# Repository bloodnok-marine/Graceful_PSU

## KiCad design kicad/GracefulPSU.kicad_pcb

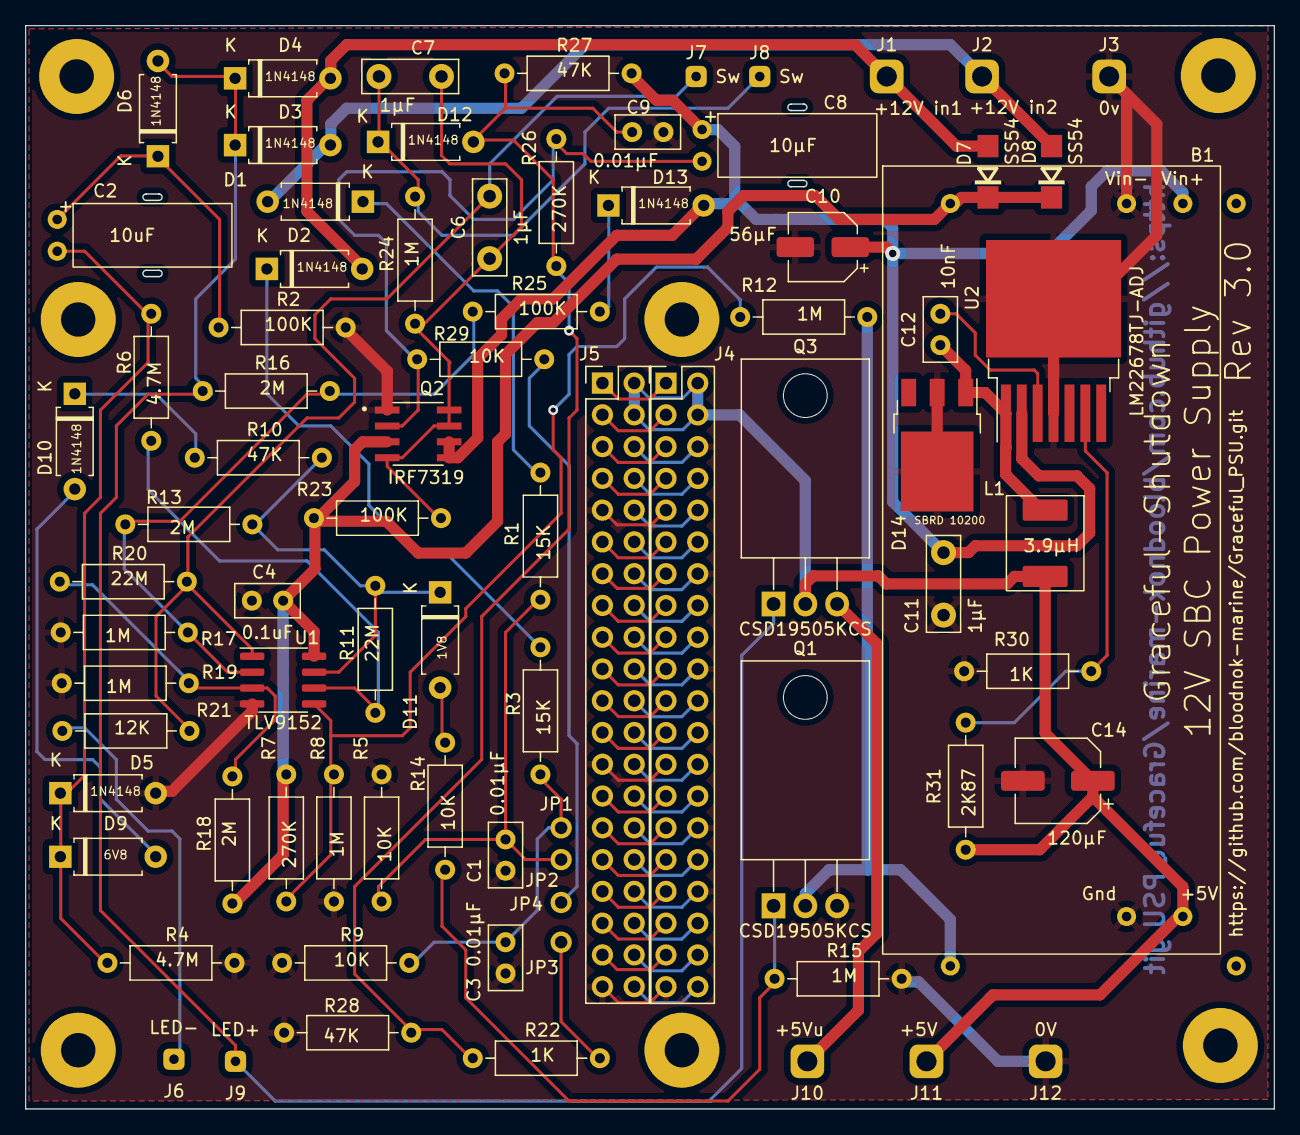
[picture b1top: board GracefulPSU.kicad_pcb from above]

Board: 2 copper layers, 99.8 x 86.6 mm, 88 parts (1 on the bottom side), 66 nets.

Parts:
B1: PSU_Board; Buck Power Supply Board
C1, C3, C9: 0.01μF; C_Disc_D5.0mm_W2.5mm_P2.50mm
C2: 10uF; Capacitor_THT_HorizRadial_D5_P2_H12
C4: 0.1uF; C_Disc_D5.0mm_W2.5mm_P2.50mm
C5: 1.6F; SuperCapacitor Module
C6, C7, C11: 1μF; C_Disc_D7.5mm_W2.5mm_P5.00mm
C8: 10μF; Capacitor_THT_HorizRadial_D5_P2_H12
C10: 56μF; CP_Elec_5x5.3
C12: 10nF; C_Disc_D5.0mm_W2.5mm_P2.50mm
C14: 120μF; CP_Elec_6.3x5.9
D1, D2, D3, D4, D5, D6, D10, D12, D13: 1N4148; my_diode_7.62_h
D7, D8: SS54; DO-214AC
D9: 6V8; my_diode_7.62_h
D11: 1V8; my_diode_7.62_h
D14: SBRD 10200; TO-252-3_TabPin2
H1, H2, H8: (no value)
H3, H4, H5, H6: pihole
J1: +12V in1; SolderConnector - HighCurrent
J2: +12V in2; SolderConnector - HighCurrent
J3: 0v; SolderConnector - HighCurrent
J4, J5: Conn_02x20; PinHeader_2x20_P2.54mm_Vertical
J6: LED-; SolderConnector
J7, J8: Sw; SolderConnector
J9: LED+; SolderConnector
J10: +5Vu; SolderConnector - HighCurrent
J11: +5V; SolderConnector - HighCurrent
J12: 0V; SolderConnector - HighCurrent
JP1, JP2, JP3, JP4: Jumper; Half-Jumper
L1: 3.9μH; Shenzhen MWSA0604S
Q1, Q3: CSD19505KCS; TO-220-3_Horizontal_TabDown
Q2: IRF7319; SOIC127P600X175-8N
R1, R3: 15K; my_resistor_6.3_2.5_10.16
R2, R23, R25: 100K; my_resistor_6.3_2.5_10.16
R4, R6: 4.7M; my_resistor_6.3_2.5_10.16
R5, R9, R14, R29: 10K; my_resistor_6.3_2.5_10.16
R7, R26: 270K; my_resistor_6.3_2.5_10.16
R8, R12, R15, R17, R19, R24: 1M; my_resistor_6.3_2.5_10.16
R10, R27, R28: 47K; my_resistor_6.3_2.5_10.16
R11, R20: 22M; my_resistor_6.3_2.5_10.16
R13, R16, R18: 2M; my_resistor_6.3_2.5_10.16
R21: 12K; my_resistor_6.3_2.5_10.16
R22, R30: 1K; my_resistor_6.3_2.5_10.16
R31: 2K87; my_resistor_6.3_2.5_10.16
U1: TLV9152; SOIC-8_3.9x4.9mm_P1.27mm
U2: LM22678TJ-ADJ; TO-263-7_TabPin8

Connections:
+5V: B1.1 (+5V), C14.1, J4.2, J4.4, J5.2, J5.4, J11.1, L1.2, Q3.2 (D), R31.2
GND: B1.2 (Gnd), B1.4 (Vin-), C1.1, C3.2, C4.2, C9.2, C10.2, C11.2, C14.2, D5.2 (A), D14.2 (A), J3.1, J4.6, J4.9, J4.14, J4.20, J4.25, J4.30, J4.34, J4.39, J5.6, J5.9, J5.14, J5.20, J5.25, J5.30, J5.34, J5.39, J12.1, Q1.3 (S), Q2.1 (S1), R2.2, R4.2, R5.1, R8.2, R9.1, R15.2, R17.2, R19.2, R28.2, R30.2, U1.4 (V-), U2.4 (GND), U2.8 (GND)
unnamed: B1.3 (Vin+), C8.1, C10.1, C11.1, D13.2 (A), Q2.5 (D2), Q2.6 (D2), R27.2, U2.2 (VIN)
unnamed: C1.2, JP2.1 (A), R1.2, R5.2
unnamed: C2.1, D6.1 (K), R2.1
unnamed: C2.2, D5.1 (K), D9.1 (K), R4.1, R6.1
unnamed: C3.1, JP1.1 (A), R3.2, R9.2
unnamed: C4.1, C5.1, D7.1 (K), D8.1 (K), Q2.3 (S2), R7.1, R18.1, R23.1, U1.8 (V+)
unnamed: C5.2, Q1.2 (D), R12.2
unnamed: C6.1, C7.1, Q2.4 (G2), Q2.7 (D1), Q2.8 (D1), R23.2, R24.1
unnamed: C6.2, J7.1, R20.2, R21.2, U1.1
unnamed: C7.2, D12.1 (K), J8.1, R24.2
unnamed: C8.2, Q2.2 (G1), R26.1, R29.1
unnamed: C9.1, D12.2 (A), R22.1, R26.2, R27.1, R28.1
unnamed: C12.1, U2.3 (BOOT)
unnamed: C12.2, D14.1 (K), L1.1, U2.1 (SW)
unnamed: D1.1 (K), R1.1
unnamed: D1.2 (A), D3.2 (A), D8.2 (A), J2.1
unnamed: D2.1 (K), R3.1
unnamed: D2.2 (A), D4.2 (A), D7.2 (A), J1.1
unnamed: D3.1 (K), D4.1 (K), D6.2 (A), J9.1, Q3.1 (G), R16.1
unnamed: D10.1 (K), R10.1
unnamed: D9.2 (A), D10.2 (A)
unnamed: D11.1 (K), R10.2, R11.2, R13.1, U1.7
unnamed: D11.2 (A), R14.1
unnamed: D13.1 (K), R25.2
unnamed: J4.1, J5.1
unnamed: J4.3, J5.3
unnamed: J4.5, J5.5
unnamed: J4.7, J5.7
unnamed: J4.8, J5.8
unnamed: J4.10, J5.10
unnamed: J4.11, J5.11
unnamed: J4.12, J5.12
unnamed: J4.13, J5.13
unnamed: J4.15, J5.15
unnamed: J4.16, J5.16
unnamed: J4.17, J5.17
unnamed: J4.18, J5.18
unnamed: J4.19, J5.19
unnamed: J4.21, J5.21
unnamed: J4.22, J5.22
unnamed: J4.23, J5.23
unnamed: J4.24, J5.24
unnamed: J4.26, J5.26
unnamed: J4.27, J5.27
unnamed: J4.28, J5.28
unnamed: J4.29, J5.29
unnamed: J4.31, J5.31
unnamed: J4.32, J5.32
unnamed: J4.33, J5.33
unnamed: J4.35, J5.35
unnamed: J4.36, J5.36
unnamed: J4.37, J5.37
unnamed: J4.38, J5.38
unnamed: J4.40, J5.40
unnamed: J6.1, R21.1
unnamed: J10.1, Q3.3 (S)
unnamed: JP3.1 (A), R22.2
unnamed: JP4.1 (A), R29.2
unnamed: Q1.1 (G), R14.2, R15.1
unnamed: R6.2, R11.1, U1.6 (-)
unnamed: R7.2, R8.1, R12.1, U1.5 (+)
unnamed: R13.2, R16.2, R17.1, R25.1, U1.2 (-)
unnamed: R18.2, R19.1, R20.1, U1.3 (+)
unnamed: R30.1, R31.1, U2.6 (FB)

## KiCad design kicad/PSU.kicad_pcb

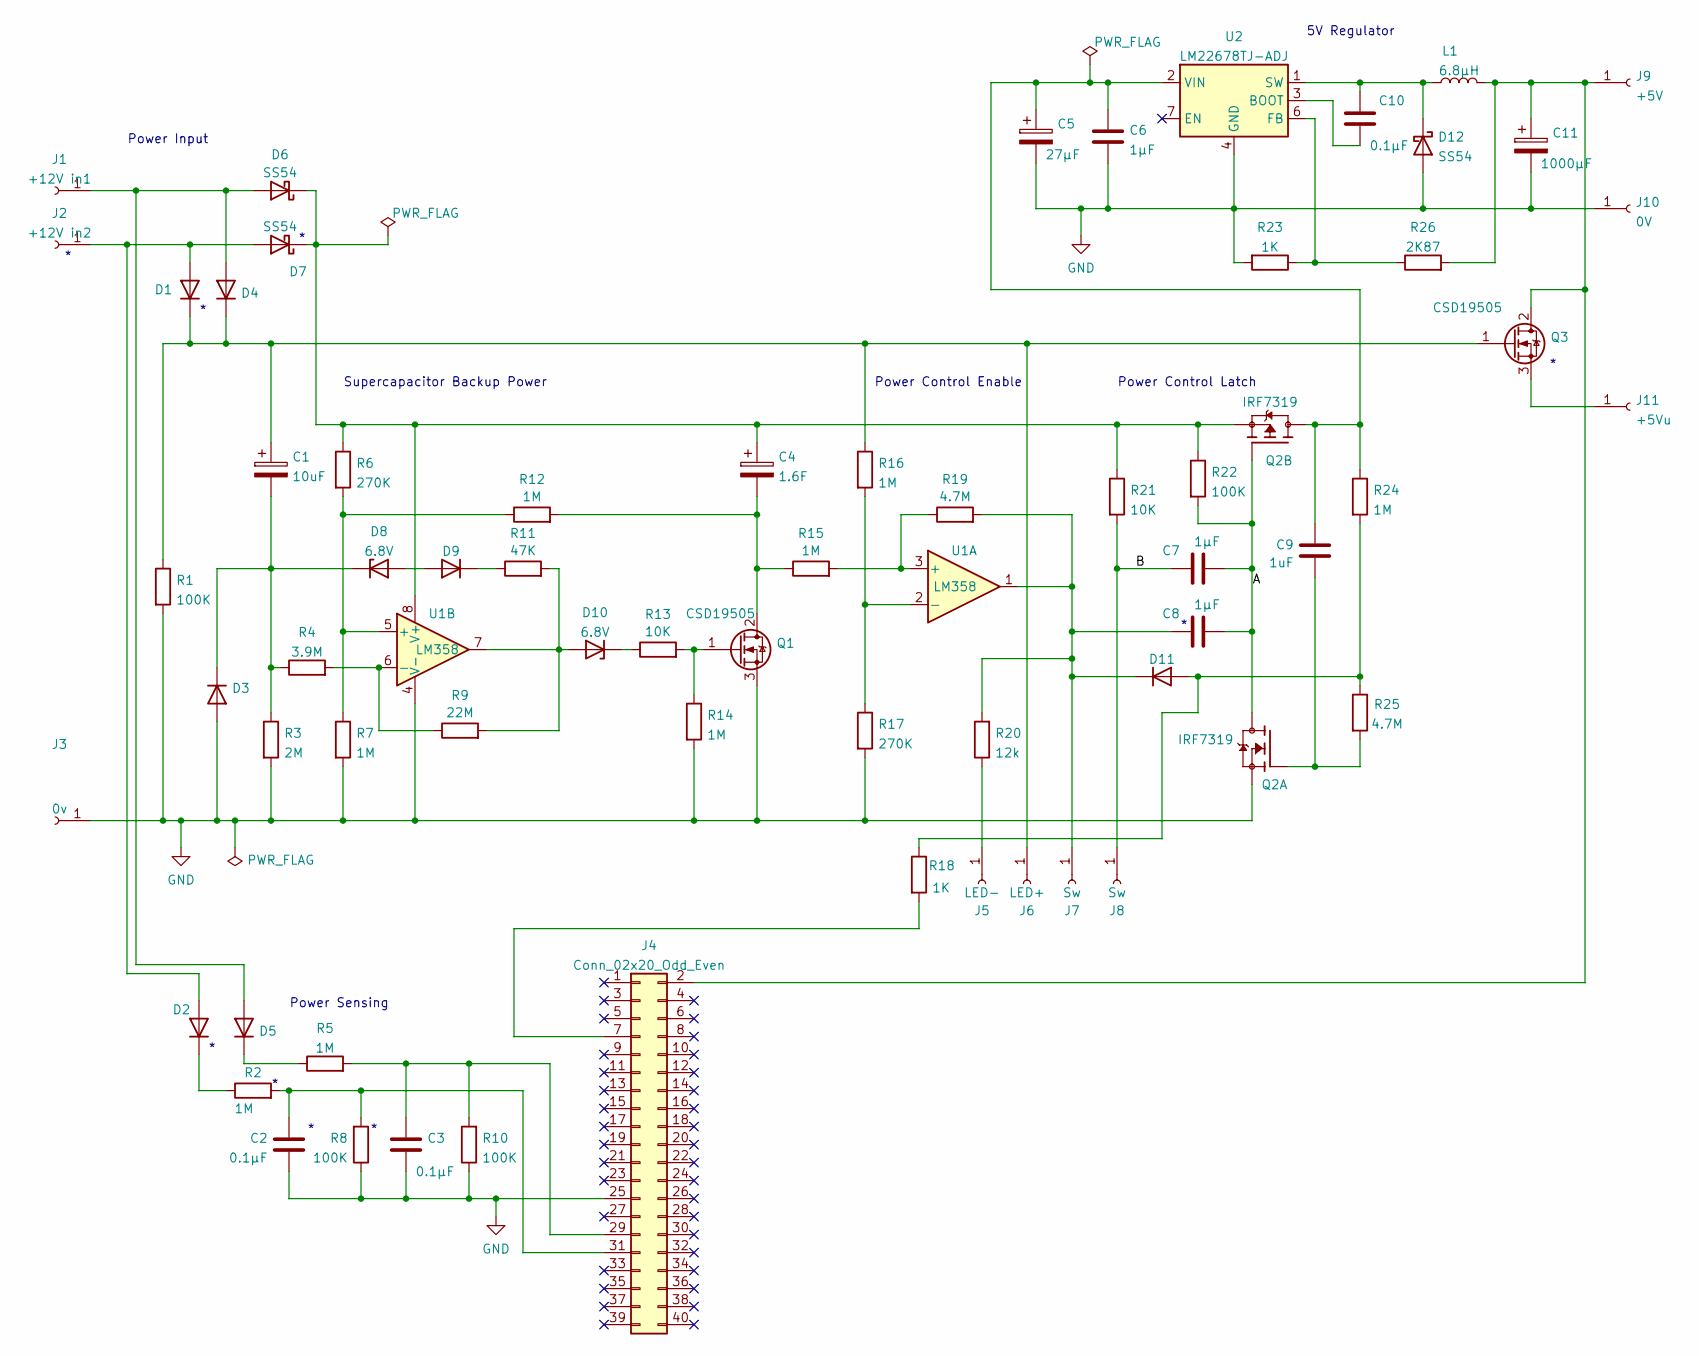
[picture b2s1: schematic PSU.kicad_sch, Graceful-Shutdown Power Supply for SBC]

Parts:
C1: 10uF; CP_Radial_D5.0mm_P2.00mm
C2, C3, C10: 0.1μF; C_Disc_D5.0mm_W2.5mm_P2.50mm
C4: 1.6F; SuperCapacitor Module
C5: 27μF; CP_Radial_D5.0mm_P2.00mm
C6, C7, C8: 1μF; C_Disc_D7.5mm_W2.5mm_P5.00mm
C9: 1uF; C_Disc_D7.5mm_W2.5mm_P5.00mm
C11: 1000μF; CP_Radial_D8.0mm_P2.50mm
D1, D2, D3, D4, D5, D9, D11: D; D_A-405_P7.62mm_Horizontal
D6, D7, D12: SS54; DO-214AC
D8, D10: 6.8V; D_A-405_P7.62mm_Horizontal
J1: +12V in1; SolderConnector - HighCurrent
J2: +12V in2; SolderConnector - HighCurrent
J3: 0v; SolderConnector - HighCurrent
J4: Conn_02x20_Odd_Even; PinHeader_2x20_P2.54mm_Vertical
J5: LED-; SolderConnector
J6: LED+; SolderConnector
J7, J8: Sw; SolderConnector
J9: +5V; SolderConnector - HighCurrent
J10: 0V; SolderConnector - HighCurrent
J11: +5Vu; SolderConnector - HighCurrent
L1: 6.8μH; L_Bourns-SRU1028_10.0x10.0mm
Q1, Q3: CSD19505; TO-220-3_Vertical
Q2: IRF7319; SOIC127P600X175-8N
R1, R8, R10, R22: 100K; R_Axial_DIN0207_L6.3mm_D2.5mm_P10.16mm_Horizontal
R2, R5, R7, R12, R14, R15, R16, R24: 1M; R_Axial_DIN0207_L6.3mm_D2.5mm_P10.16mm_Horizontal
R3: 2M; R_Axial_DIN0207_L6.3mm_D2.5mm_P10.16mm_Horizontal
R4: 3.9M; R_Axial_DIN0207_L6.3mm_D2.5mm_P10.16mm_Horizontal
R6, R17: 270K; R_Axial_DIN0207_L6.3mm_D2.5mm_P10.16mm_Horizontal
R9: 22M; R_Axial_DIN0207_L6.3mm_D2.5mm_P10.16mm_Horizontal
R11: 47K; R_Axial_DIN0207_L6.3mm_D2.5mm_P10.16mm_Horizontal
R13, R21: 10K; R_Axial_DIN0207_L6.3mm_D2.5mm_P10.16mm_Horizontal
R18, R23: 1K; R_Axial_DIN0207_L6.3mm_D2.5mm_P10.16mm_Horizontal
R19, R25: 4.7M; R_Axial_DIN0207_L6.3mm_D2.5mm_P10.16mm_Horizontal
R20: 12k; R_Axial_DIN0207_L6.3mm_D2.5mm_P10.16mm_Horizontal
R26: 2K87; R_Axial_DIN0207_L6.3mm_D2.5mm_P10.16mm_Horizontal
U1: LM358; DIP-8_W7.62mm
U2: LM22678TJ-ADJ; TO-263-7_TabPin8

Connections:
/A: C7.1, C8.1, Q2.4 (G2), Q2.7 (D1), Q2.8 (D1), R22.2
/B: C7.2, J8.1, R21.2
GND: C2.1, C3.2, C5.2, C6.2, C11.2, D3.2 (A), D12.2 (A), J3.1, J4.25, J10.1, Q1.3 (S), Q2.1 (S1), R1.2, R3.2, R7.2, R8.1, R10.1, R14.2, R17.2, R23.2, U1.4 (V-), U2.4 (GND), U2.8 (GND)
unnamed: C1.1, D1.1 (K), D4.1 (K), J6.1, Q3.1 (G), R1.1, R16.1
unnamed: C2.2, J4.31, R2.2, R8.2
unnamed: C3.1, J4.29, R5.2, R10.2
unnamed: C4.1, D6.1 (K), D7.1 (K), Q2.3 (S2), R6.1, R21.1, R22.1, U1.8 (V+)
unnamed: C4.2, Q1.2 (D), R12.2, R15.1
unnamed: C5.1, C6.1, C9.2, Q2.5 (D2), Q2.6 (D2), R24.1, U2.2 (VIN)
unnamed: C8.2, D11.1 (K), J7.1, R19.2, R20.2, U1.1
unnamed: C9.1, Q2.2 (G1), R25.2
unnamed: C10.1, U2.3 (BOOT)
unnamed: C10.2, D12.1 (K), L1.1, U2.1 (SW)
unnamed: C11.1, J4.2, J9.1, L1.2, Q3.2 (D), R26.2
unnamed: D1.2 (A), D2.2 (A), D7.2 (A), J2.1
unnamed: D2.1 (K), R2.1
unnamed: D4.2 (A), D5.2 (A), D6.2 (A), J1.1
unnamed: D5.1 (K), R5.1
unnamed: C1.2, D3.1 (K), D8.1 (K), R3.1, R4.1
unnamed: D8.2 (A), D9.2 (A)
unnamed: D9.1 (K), R11.1
unnamed: D10.1 (K), R13.1
unnamed: D10.2 (A), R9.2, R11.2, U1.7
unnamed: D11.2 (A), R18.1, R24.2, R25.1
unnamed: J4.7, R18.2
unnamed: J5.1, R20.1
unnamed: J11.1, Q3.3 (S)
unnamed: Q1.1 (G), R13.2, R14.1
unnamed: R4.2, R9.1, U1.6 (-)
unnamed: R6.2, R7.1, R12.1, U1.5 (+)
unnamed: R15.2, R19.1, U1.3 (+)
unnamed: R16.2, R17.1, U1.2 (-)
unnamed: R23.1, R26.1, U2.6 (FB)

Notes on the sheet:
Power Control Latch
Supercapacitor Backup Power
5V Regulator
Power Input
Power Control Enable
Power Sensing

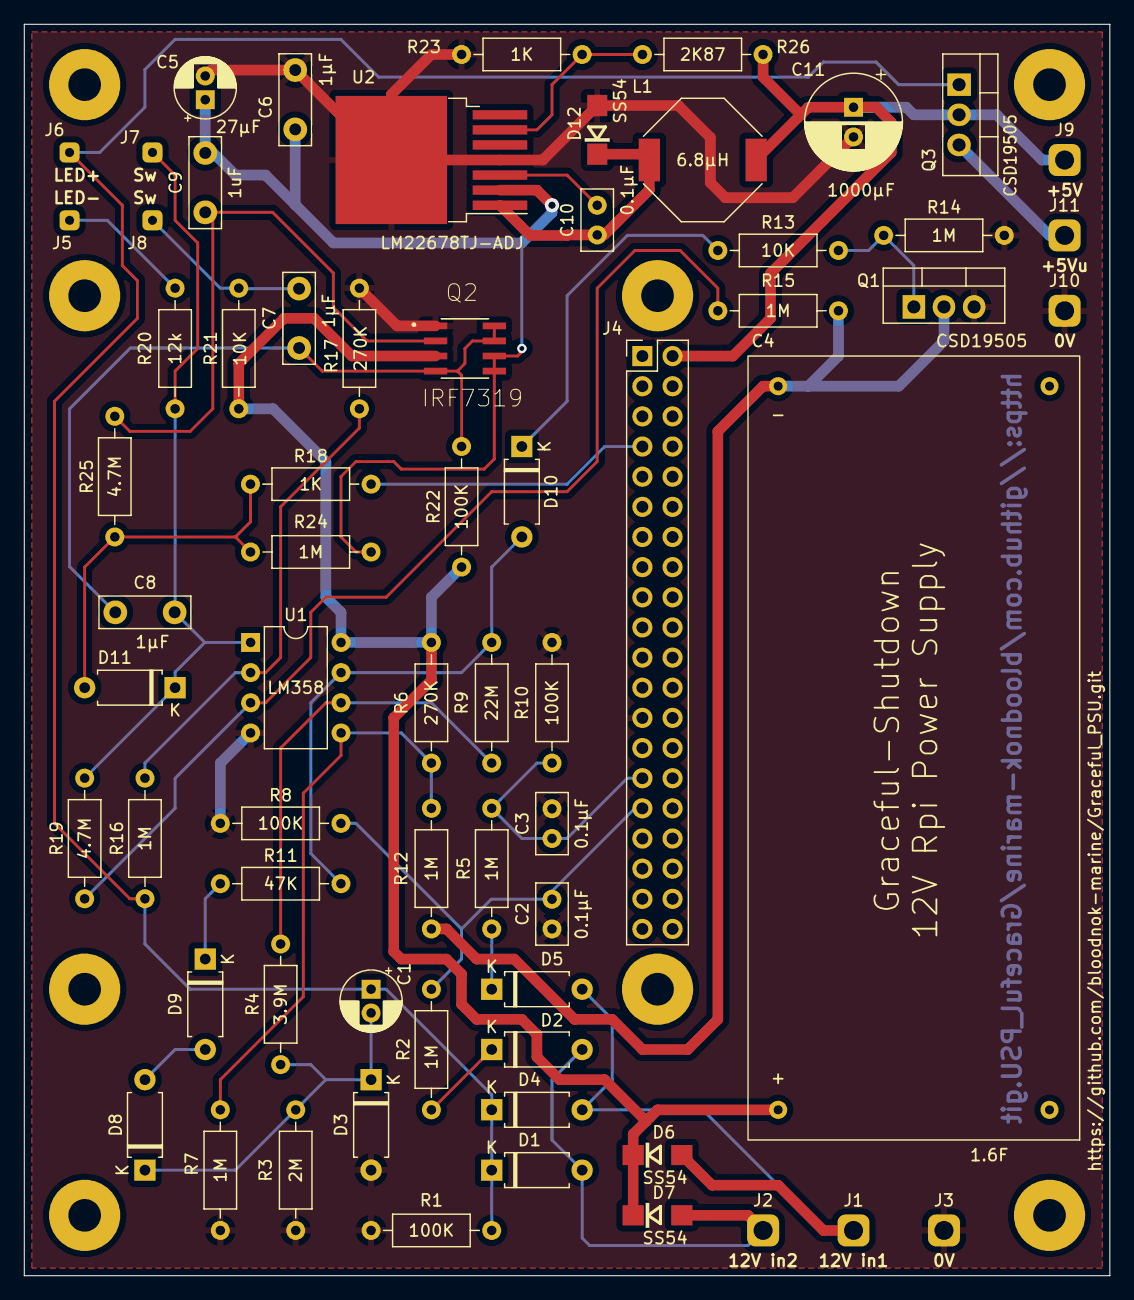
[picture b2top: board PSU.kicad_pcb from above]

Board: 2 copper layers, 91.4 x 105.4 mm, 66 parts (0 on the bottom side), 33 nets.

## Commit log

2022-11-05 First release to github.
2022-11-05 Updated schematic in line with latest changes.
2022-11-06 Removed old, incorrect for this project, pcb gerber files.
2023-04-02 Initial release of revision 2. Fixes from prototyping and experiments.
2023-11-12 Release of version sent for pcb manufacture.
2024-03-26 Prep for release to github.
2024-03-27 Preparing for release to github.
2024-03-27 Prep to send R3.0 board to the manufacturer.
